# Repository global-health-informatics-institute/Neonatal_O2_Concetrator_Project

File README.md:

# Neonatal_O2_Concetrator_Project
All files used in the Neonatal Oxygen Concentrator Project
  * Endcap design (Fusion360)
  * Solid State Relay PWM Arduino code
  * Oxygen Sensor Arduino code
  * Rotary Valve driver Arduino code
  * Integrated Arduino code of all the arduino codes

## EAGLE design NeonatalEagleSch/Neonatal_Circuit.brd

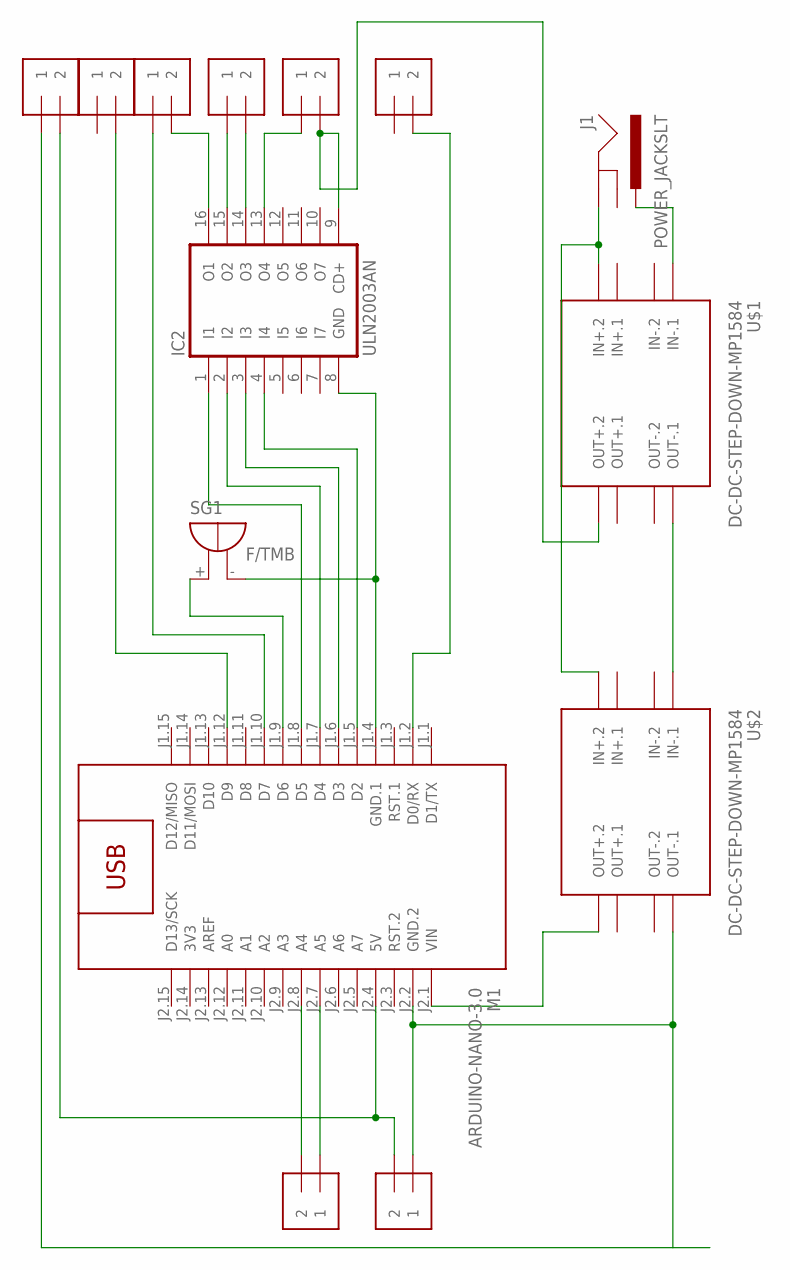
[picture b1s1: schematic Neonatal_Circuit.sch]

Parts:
IC2: ULN2003AN; DIL16
J1: POWER_JACKSLT; POWER_JACK_SLOT
J2, J3, J4, J5, J6, J7, J8, J9: 1X2-3.5MM
M1: ARDUINO-NANO-3.0
SG1: F/TMB
U$1, U$2: DC-DC-STEP-DOWN-MP1584

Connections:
3V3: M1.J2.14 (3V3)
unnamed: IC2.4 (I4), M1.J1.5 (D2)
unnamed: IC2.3 (I3), M1.J1.6 (D3)
unnamed: IC2.2 (I2), M1.J1.7 (D4)
unnamed: IC2.1 (I1), M1.J1.8 (D5)
unnamed: J1.PWR, U$1.IN-.1
unnamed: J1.GND@2 (GND), U$1.IN+.2, U$2.IN+.2
unnamed: U$1.OUT-.1, U$2.IN-.1
unnamed: M1.J2.1 (VIN), U$2.OUT+.2
unnamed: IC2.16 (O1), J6.2
unnamed: IC2.15 (O2), J5.1
unnamed: IC2.14 (O3), J5.2
unnamed: IC2.13 (O4), J4.1
unnamed: IC2.8 (GND), M1.J1.4 (GND.1), SG1.-
unnamed: M1.J1.9 (D6), SG1.+
unnamed: J2.2, M1.J1.12 (D9)
unnamed: J7.2, J8.2, M1.J2.4 (5V)
unnamed: J3.2, M1.J1.2 (D0/RX)
unnamed: J9.1, M1.J2.7 (A5)
unnamed: J9.2, M1.J2.8 (A4)
unnamed: IC2.9 (CD+), J4.2, U$1.OUT+.2
unnamed: J7.1, J8.1, M1.J2.2 (GND.2), U$2.OUT-.1
unnamed: J6.1, M1.J1.10 (D7)

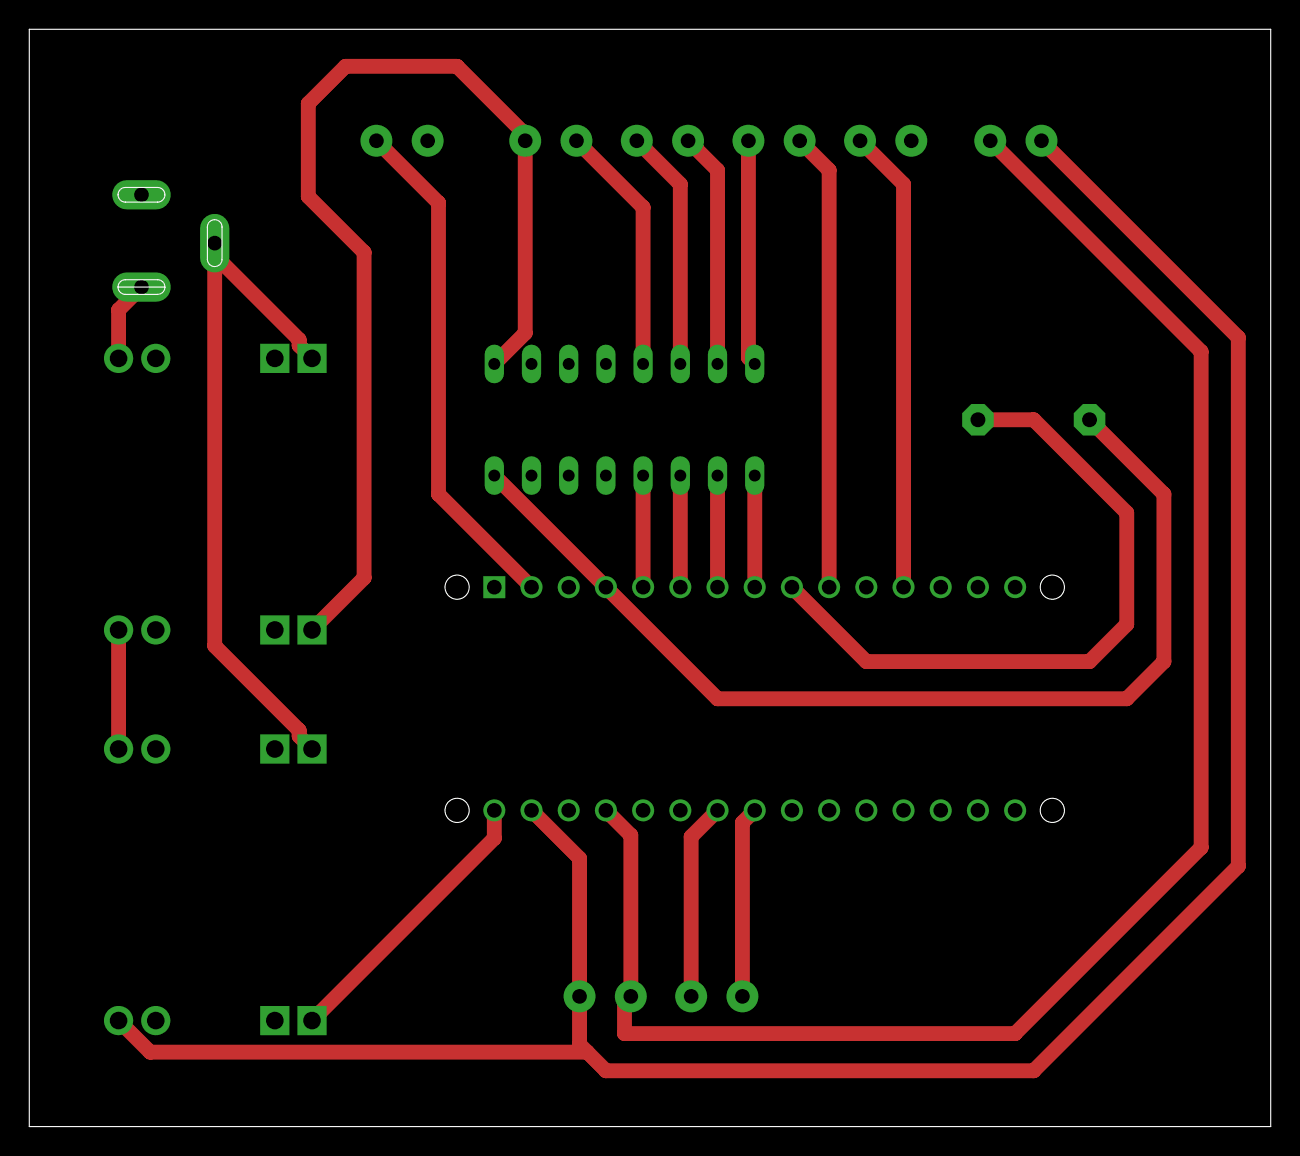
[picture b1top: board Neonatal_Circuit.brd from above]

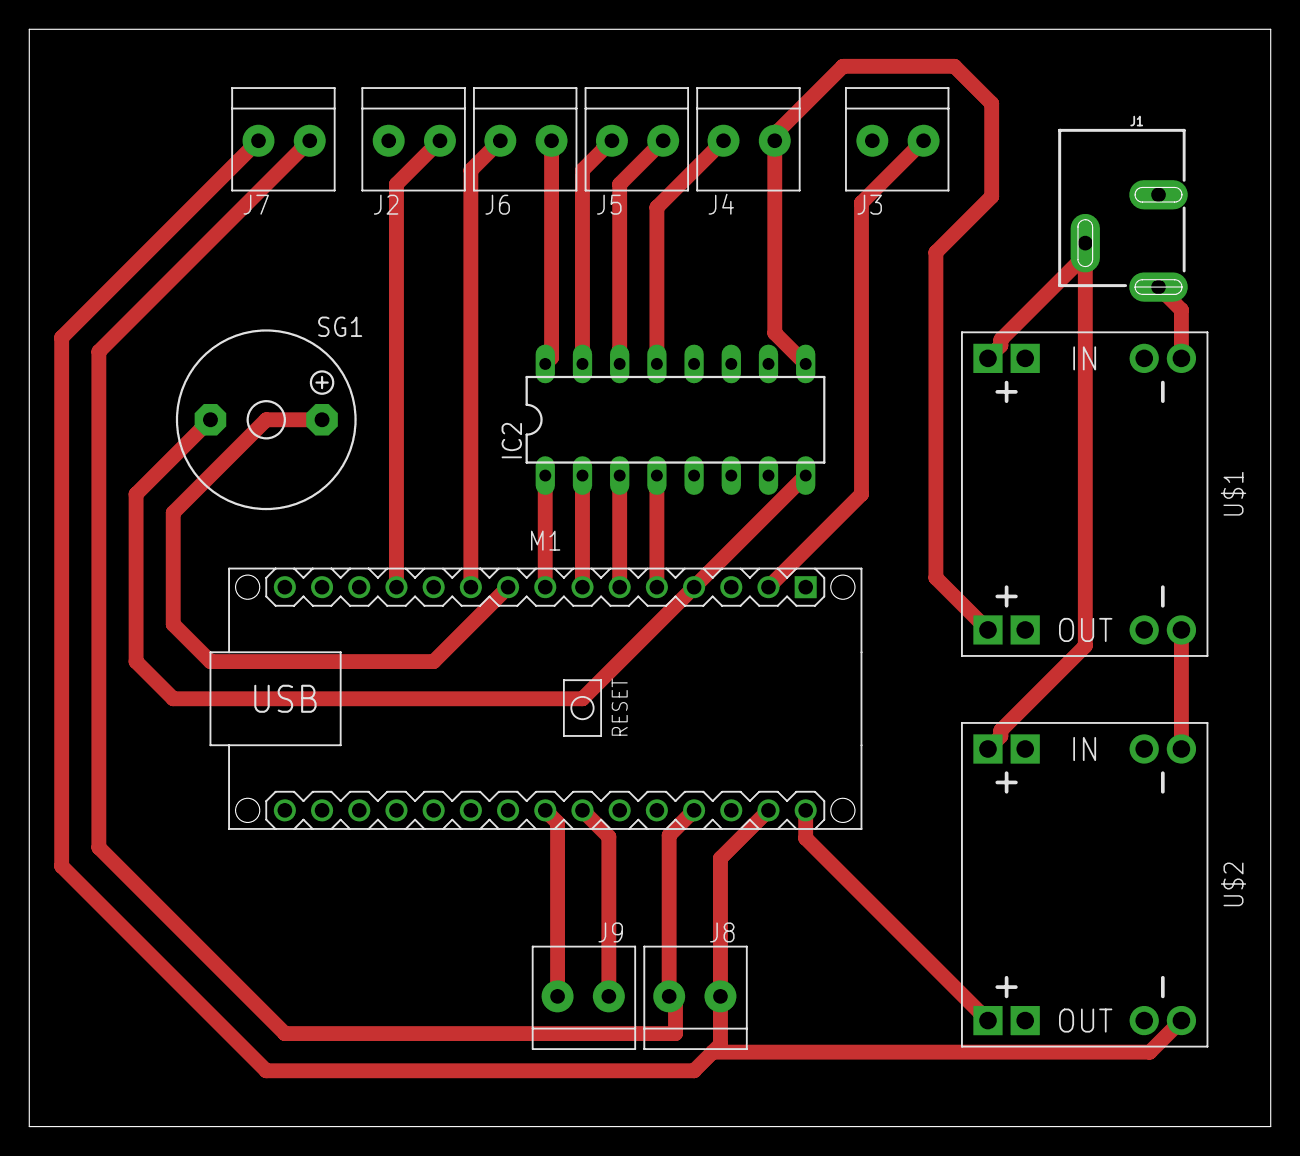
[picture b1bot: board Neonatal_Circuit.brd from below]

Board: 2 copper layers, 84.8 x 74.9 mm, 14 parts (14 on the bottom side), 22 nets.

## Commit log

2023-05-29 Add files via upload
    The code communicates with an Analog-to-Digital Converter (ADC) using the SPI protocol. It reads an analog voltage from channel 0 of the ADC and performs actions based on the voltage value.
    The sketch starts by setting up the necessary pins and initializing the SPI communication. In the main loop, it sends commands to the ADC to request a voltage reading. It then combines the received b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
    The voltage value is printed to the serial monitor along with the ADC reading. If the ADC reading is above a certain threshold (500), it toggles an LED connected to pin 7.
    Over
2023-05-29 Add files via upload
    This is a schematic and PCB design of the control board used for the Neonatal Oxygen Concentrator
2025-02-11 KiCad files for the neonatal circuit

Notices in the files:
parts and their libraries:
GHIISparkFun-Connectors: Licensing: Creative Commons ShareAlike 4.0 International - https://creativecommons.org/licenses/by-sa/4.0
GHIdiy-modules: Released under the Creative Commons Attribution 4.0 International License: http://creativecommons.org/licenses/by/4.0
